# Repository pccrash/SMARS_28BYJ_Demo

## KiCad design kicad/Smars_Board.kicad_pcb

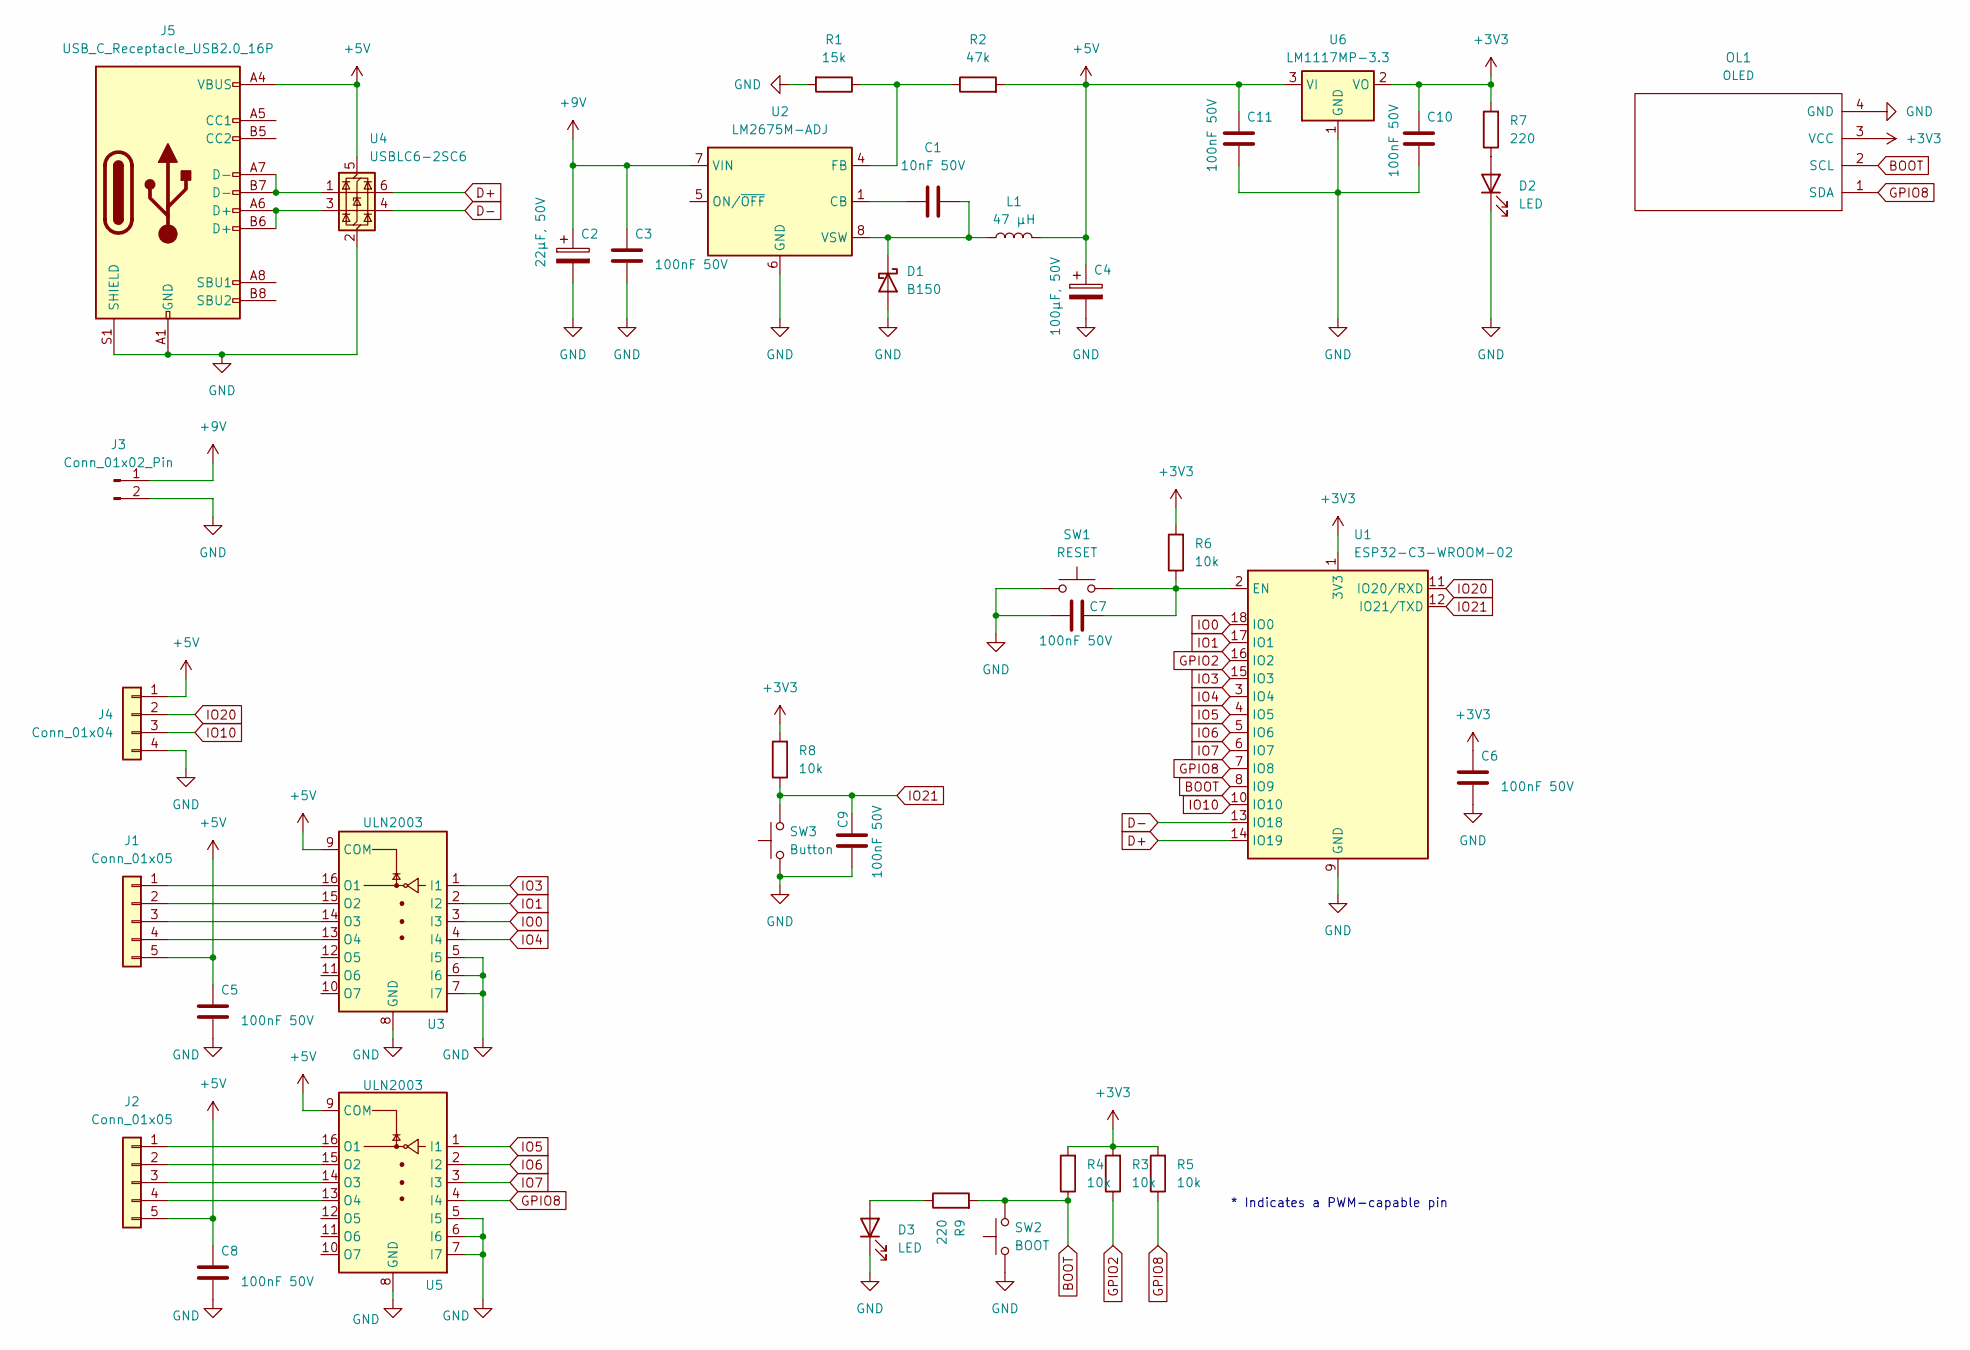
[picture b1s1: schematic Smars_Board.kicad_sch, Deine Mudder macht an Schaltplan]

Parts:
C1: 10nF 50V; C_0805_2012Metric_Pad1.18x1.45mm_HandSolder
C2: 22µF, 50V; CP_Elec_6.3x5.8
C3, C5, C6, C7, C8, C9, C10, C11: 100nF 50V; C_0805_2012Metric_Pad1.18x1.45mm_HandSolder
C4: 100µF, 50V; CP_Elec_10x10.5
D1: B150; D_SMA_Handsoldering
D2, D3: LED; LED_0805_2012Metric
J1, J2: Conn_01x05; JST_XH_B5B-XH-A_1x05_P2.50mm_Vertical
J3: Conn_01x02_Pin; JST_XH_B2B-XH-A_1x02_P2.50mm_Vertical
J4: Conn_01x04; PinSocket_1x04_P2.54mm_Vertical
J5: USB_C_Receptacle_USB2.0_16P; USB_C_Receptacle_GCT_USB4110
L1: 47 µH; L_Ferrocore_DLG-1004
OL1: OLED; OLED_128x64
R1: 15k; R_0805_2012Metric_Pad1.20x1.40mm_HandSolder
R2: 47k; R_0805_2012Metric_Pad1.20x1.40mm_HandSolder
R3, R4, R5, R6, R8: 10k; R_0805_2012Metric_Pad1.20x1.40mm_HandSolder
R7, R9: 220; R_0805_2012Metric_Pad1.20x1.40mm_HandSolder
SW1: RESET; SW_Push_1P1T_NO_CK_KSC7xxJ
SW2: BOOT; SW_Push_1P1T_NO_CK_KSC7xxJ
SW3: Button; SW_Push_1P1T_NO_CK_KSC7xxJ
U1: ESP32-C3-WROOM-02
U2: LM2675M-ADJ; SOIC-8_3.9x4.9mm_P1.27mm
U3, U5: ULN2003; SOIC-16_3.9x9.9mm_P1.27mm
U4: USBLC6-2SC6; SOT-23-6
U6: LM1117MP-3.3; SOT-223-3_TabPin2

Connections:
+3V3: C6.2, C10.2, OL1.3 (VCC), R3.2, R4.2, R5.2, R6.2, R7.2, R8.2, U1.1 (3V3), U6.2 (VO)
+5V: C4.1, C5.2, C8.2, C11.2, J1.5, J2.5, J4.1, J5.A4 (VBUS), J5.A9 (VBUS), J5.B4 (VBUS), J5.B9 (VBUS), L1.2, R2.2, U3.9 (COM), U4.5 (VBUS), U5.9 (COM), U6.3 (VI)
+9V: C2.1, C3.2, J3.1, U2.7 (VIN)
BOOT: OL1.2 (SCL), R4.1, R9.2, SW2.2, U1.8 (IO9)
D+: U1.14 (IO19), U4.6 (I/O1)
D-: U1.13 (IO18), U4.4 (I/O2)
GND: C2.2, C3.1, C4.2, C5.1, C6.1, C7.2, C8.1, C9.2, C10.1, C11.1, D1.2 (A), D2.1 (K), D3.1 (K), J3.2, J4.4, J5.A1 (GND), J5.A12 (GND), J5.B1 (GND), J5.B12 (GND), J5.S1 (SHIELD), OL1.4 (GND), R1.2, SW1.1, SW2.1, SW3.1, U1.9 (GND), U1.19 (GND), U2.6 (GND), U3.5 (I5), U3.6 (I6), U3.7 (I7), U3.8 (GND), U4.2 (GND), U5.5 (I5), U5.6 (I6), U5.7 (I7), U5.8 (GND), U6.1 (GND)
GPIO2: R3.1, U1.16 (IO2)
GPIO8: OL1.1 (SDA), R5.1, U1.7 (IO8), U5.4 (I4)
IO0: U1.18 (IO0), U3.3 (I3)
IO1: U1.17 (IO1), U3.2 (I2)
IO3: U1.15 (IO3), U3.1 (I1)
IO4: U1.3 (IO4), U3.4 (I4)
IO5: U1.4 (IO5), U5.1 (I1)
IO6: U1.5 (IO6), U5.2 (I2)
IO7: U1.6 (IO7), U5.3 (I3)
IO10: J4.3, U1.10 (IO10)
IO20: J4.2, U1.11 (IO20/RXD)
IO21: C9.1, R8.1, SW3.2, U1.12 (IO21/TXD)
unnamed: C1.2, D1.1 (K), L1.1, U2.8 (VSW)
unnamed: D2.2 (A), R7.1
unnamed: D3.2 (A), R9.1
unnamed: J1.1, U3.16 (O1)
unnamed: J1.2, U3.15 (O2)
unnamed: J1.3, U3.14 (O3)
unnamed: J1.4, U3.13 (O4)
unnamed: J2.1, U5.16 (O1)
unnamed: J2.2, U5.15 (O2)
unnamed: J2.3, U5.14 (O3)
unnamed: J2.4, U5.13 (O4)
unnamed: J5.A6 (D+), J5.B6 (D+), U4.3 (I/O2)
unnamed: J5.A7 (D-), J5.B7 (D-), U4.1 (I/O1)
unnamed: C7.1, R6.1, SW1.2, U1.2 (EN)
unnamed: C1.1, U2.1 (CB)
unnamed: R1.1, R2.1, U2.4 (FB)

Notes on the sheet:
* Indicates a PWM-capable pin

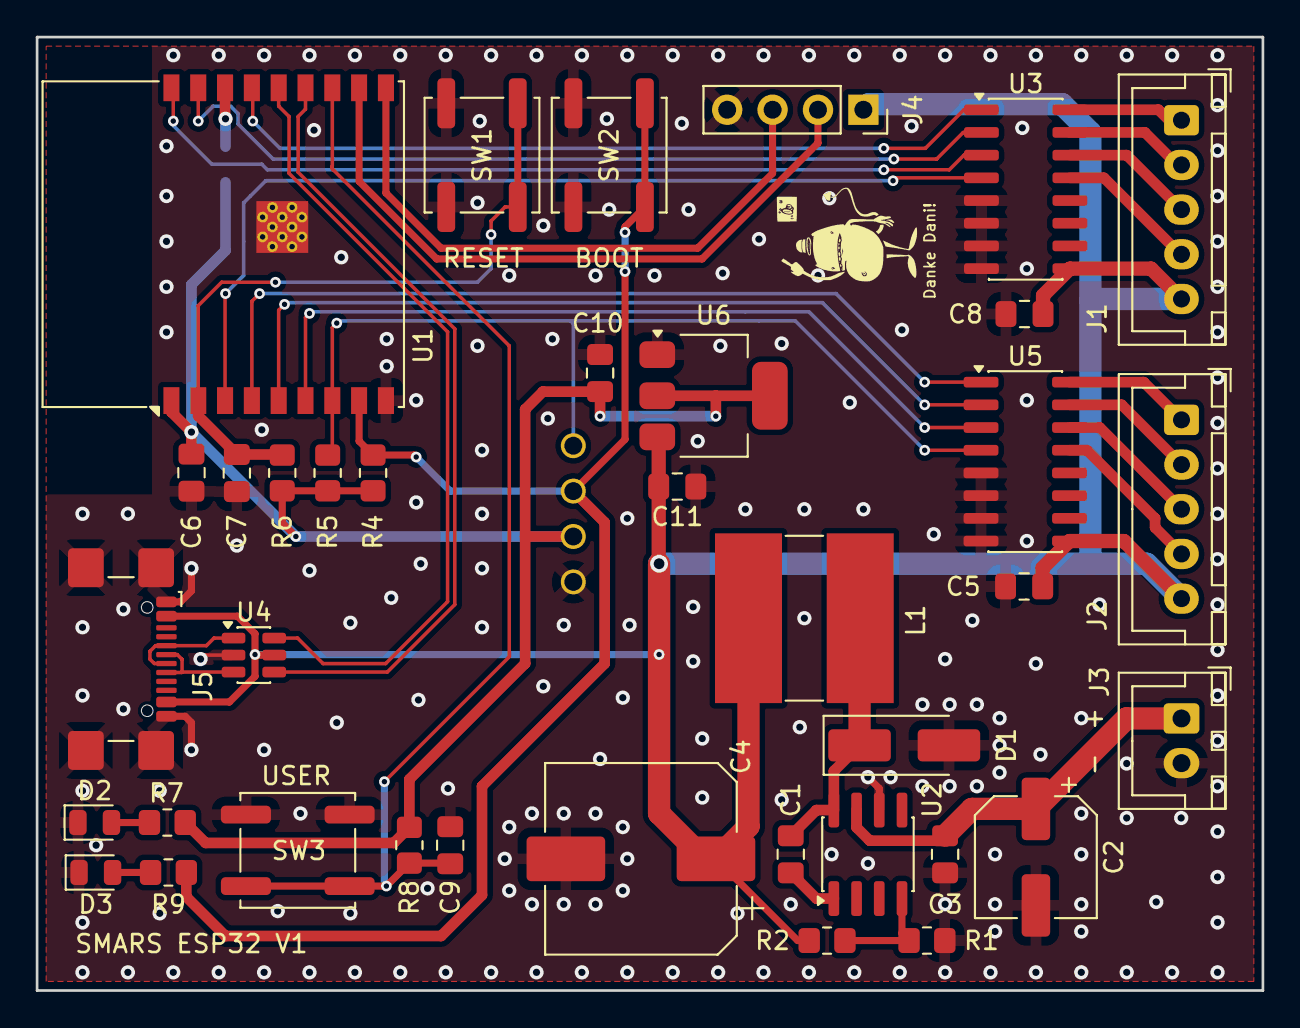
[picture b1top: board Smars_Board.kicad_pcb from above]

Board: 2 copper layers, 68.6 x 53.3 mm, 39 parts (1 on the bottom side), 35 nets.

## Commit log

2025-12-01 added KiCad files to test Git in KiCad 9
